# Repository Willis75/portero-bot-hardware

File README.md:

# Portero Bot — Hardware V2

Custom PCB and ESP32 firmware for the Claustro4 gate controller system.

## Overview

Replaces the Raspberry Pi Pico + protoboard + commercial relay board with a professional custom PCB.

- **MCU:** ESP32-WROOM-32E
- **Ethernet:** W5500 (SPI) + HanRun HR911105A RJ45
- **Relays:** 3× dry contact (simulates button press on gate opener controllers)
- **Power:** 9-24V DC barrel jack → 5V buck → 3.3V LDO
- **Programming:** MicroUSB (first flash) + OTA over Ethernet (updates)

## Repository Structure

```
hardware/       KiCad schematic + PCB layout + Gerber files
firmware/       PlatformIO ESP32 firmware (C++)
docs/           BOM, schematic reference, Flux.ai prompt
```

## API

The ESP32 exposes an HTTP API compatible with the existing Node.js bot (no changes required):

```
POST /abrir/vehicular_entrada
POST /abrir/vehicular_salida
POST /abrir/peatonal
GET  /healthz
POST /update   (OTA firmware upload)
```

## Related

- Bot: [Willis75/Portero-bot-telegram](https://github.com/Willis75/Portero-bot-telegram)
- Fabrication: JLCPCB PCBA (~$126 USD / 5 units)

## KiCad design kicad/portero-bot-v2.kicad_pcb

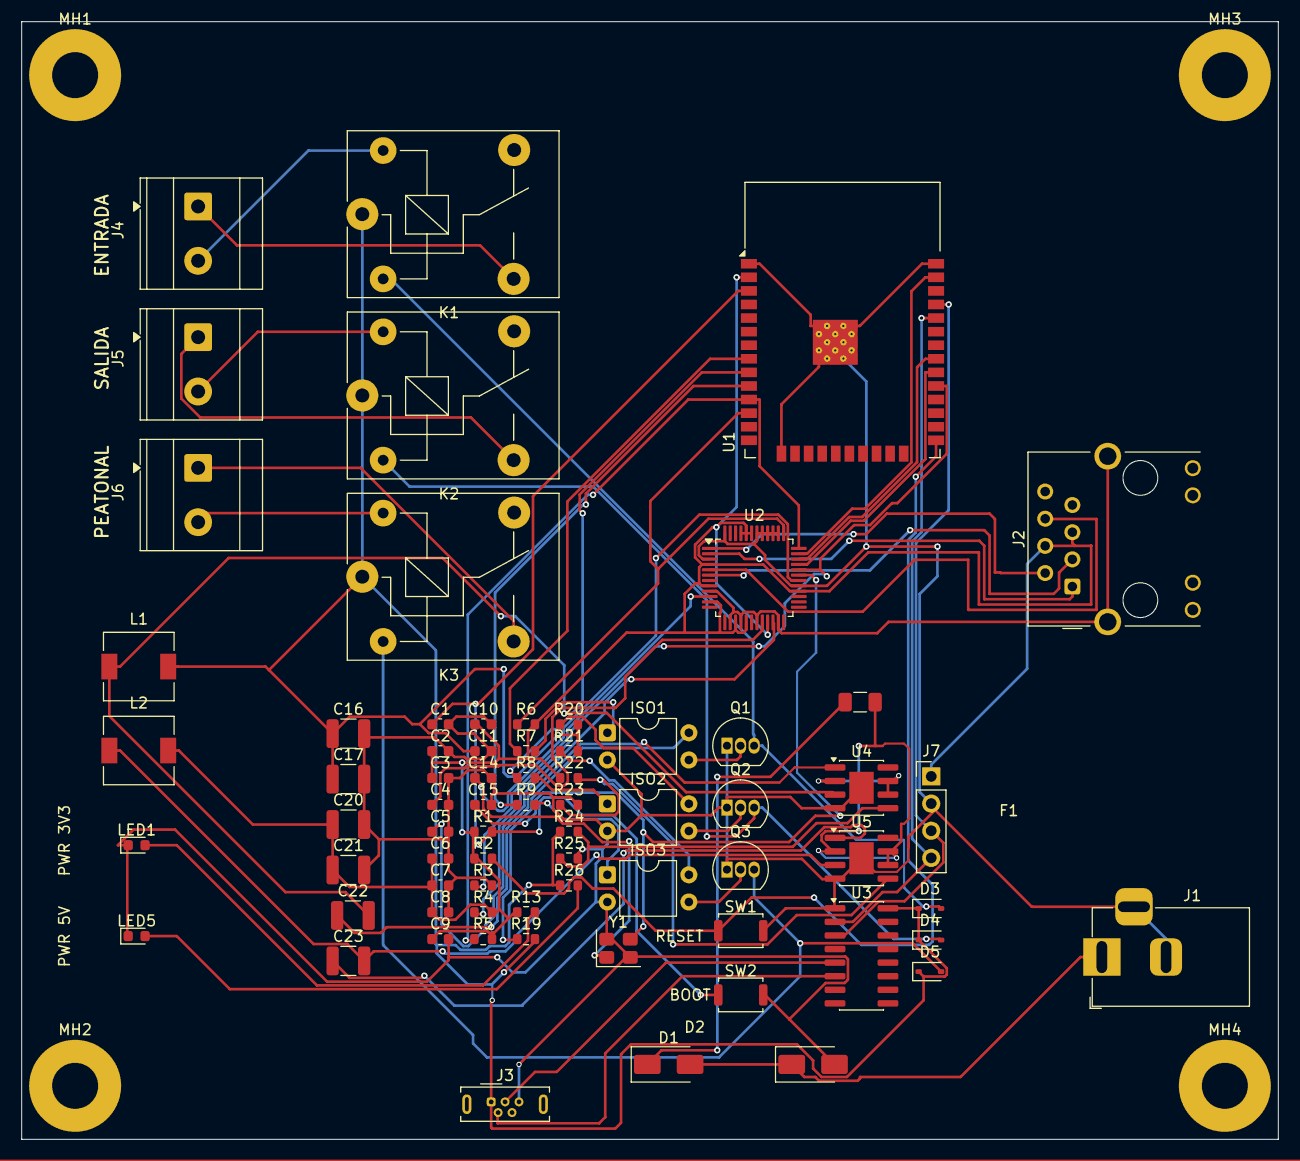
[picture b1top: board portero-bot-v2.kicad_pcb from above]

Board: 2 copper layers, 117.5 x 104.5 mm, 75 parts (0 on the bottom side), 56 nets.

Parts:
C1: 1uF; C_0603_1608Metric
C2, C3, C6, C7, C8, C9, C10, C11: 100nF; C_0603_1608Metric
C4: 4.7uF; C_0603_1608Metric
C5: 10nF; C_0603_1608Metric
C14, C15: 22pF; C_0603_1608Metric
C16, C17, C20, C21: 100uF; C_1210_3225Metric
C22, C23: 100nF; C_1210_3225Metric
D1: SS34-E3/57T; D_SMA
D2: SMAJ24CA-TR; D_SMA
D3, D4, D5: 1N5819WS-7-F; D_SOD-323
F1: 0ZCC0150BF2C; Fuse_1206_3216Metric
ISO1, ISO2, ISO3: PC817X1CSP9F; DIP-4_W7.62mm
J1: DC005; BarrelJack_Horizontal
J2: HR911105A; RJ45_Hanrun_HR911105A_Horizontal
J3: USB Micro B; USB_Micro-B_Wuerth_614105150721_Vertical
J4, J5, J6: KF301-2P; TerminalBlock_Phoenix_MKDS-3-2-5.08_1x02_P5.08mm_Horizontal
J7: Pin Header 01x04 2.54mm Vertical; PinHeader_1x04_P2.54mm_Vertical
K1, K2, K3: SRD-05VDC-SL-C; Relay_SPDT_SANYOU_SRD_Series_Form_C
L1, L2: 22uH; L_6.3x6.3_H3
LED1: KT-0603YG; LED_0603_1608Metric
LED5: KT-0603R; LED_0603_1608Metric
MH1, MH2, MH3, MH4: MountingHole_4.3mm_M4_Pad
Q1, Q2, Q3: 2N2222A; TO-92_Inline
R1, R2, R4, R5, R6, R23, R25: 10k; R_0603_1608Metric
R3: 12.4k; R_0603_1608Metric
R7, R8, R9, R13, R26: 1k; R_0603_1608Metric
R19, R20, R21: 330; R_0603_1608Metric
R22: 26.1k; R_0603_1608Metric
R24: 44.2k; R_0603_1608Metric
SW1, SW2: KH-6X6X5H-STM; SW_Push_SPST_NO_Alps_SKRK
U1: ESP32-WROOM-32E-N16; ESP32-WROOM-32
U2: W5500; LQFP-48_7x7mm_P0.5mm
U3: CH340C; SOIC-16_3.9x9.9mm_P1.27mm
U4, U5: MP2307DN-HW-LF-Z; SOIC-8-1EP_3.9x4.9mm_P1.27mm_EP2.29x3mm
Y1: NX3225GA-25MHZ-STD-CRG-2; Crystal_SMD_3225-4Pin_3.2x2.5mm

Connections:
3V3: C2.1, C3.1, C6.1, C7.1, C8.1, C9.1, C10.1, C20.1, C21.1, J2.4, J2.5, J7.1, L2.2, R1.1, R2.1, R4.2, R5.2, R6.2, R13.1, R22.1, U1.2 (3V3), U2.4 (AVDD), U2.8 (AVDD), U2.11 (AVDD), U2.15 (AVDD), U2.17 (AVDD), U2.21 (AVDD), U2.28 (VDD), U2.43 (PMODE2), U2.44 (PMODE1), U2.45 (PMODE0)
5V: C11.1, C16.1, C17.1, D3.1 (K), D4.1 (K), D5.1 (K), J3.1 (VBUS), K1.1 (A1), K2.1 (A1), K3.1 (A1), L1.2, R19.2, R20.2, R21.2, R24.1, R26.1, U3.16 (VCC)
BOOT: R2.2, SW1.1, U1.25 (IO0)
BST_3V3: C23.1, U5.1 (BS)
BST_5V: C22.1, U4.1 (BS)
EN: C1.1, R1.2, SW2.1, U1.3 (EN)
ETH_CS: R4.1, U1.29 (IO5), U2.32 (~SCS)
ETH_INT: R5.1, U1.11 (IO26), U2.36 (~INT)
ETH_RST: R6.1, U1.12 (IO27), U2.37 (~RST)
ETH_RX_N: J2.6, U2.5 (RXN)
ETH_RX_P: J2.3, U2.6 (RXP)
ETH_TX_N: J2.2, U2.1 (TXN)
ETH_TX_P: J2.1, U2.2 (TXP)
ETH_XI: C14.1, U2.30 (XI/CLKIN), Y1.1
ETH_XO: C15.1, U2.31 (XO), Y1.3
FB_3V3: R22.2, R23.1, U5.5 (FB)
FB_5V: R24.2, R25.1, U4.5 (FB)
GND: C1.2, C2.2, C3.2, C4.2, C5.2, C6.2, C7.2, C8.2, C9.2, C10.2, C11.2, C14.2, C15.2, C16.2, C17.2, C20.2, C21.2, D2.2, ISO1.2 (CATHODE), ISO2.2 (CATHODE), ISO3.2 (CATHODE), J1.2, J1.3, J2.SH, J3.5 (GND), J7.2, LED1.1, LED5.1, Q1.1 (E), Q2.1 (E), Q3.1 (E), R3.2, R23.2, R25.2, SW1.2, SW2.2, U1.1 (GND), U1.15 (GND), U1.38 (GND), U1.39 (GND), U2.3 (AGND), U2.9 (AGND), U2.14 (AGND), U2.16 (AGND), U2.19 (AGND), U2.23 (RSVD), U2.29 (GND), U2.38 (RSVD), U2.39 (RSVD), U2.40 (RSVD), U2.41 (RSVD), U2.42 (RSVD), U2.48 (AGND), U3.1 (GND), U4.4 (GND), U4.9 (EPAD), U5.4 (GND), U5.9 (EPAD), Y1.2 (GND), Y1.4 (GND)
LED5_5V_IND: LED5.2, R26.2
LED_3V3_PWR: LED1.2, R13.2
RELAY1_BASE: ISO1.3 (EMITTER), Q1.2 (B)
RELAY1_COIL_LOW: D3.2 (A), K1.2 (A2), Q1.3 (C)
RELAY1_COM: J4.1, K1.3 (COM)
RELAY1_GPIO: R7.1, U1.8 (IO32)
RELAY1_NO: J4.2, K1.5 (NO)
RELAY1_OPTO_COL: ISO1.4 (COLLECTOR), R19.1
RELAY1_OPTO_LED: ISO1.1 (ANODE), R7.2
RELAY2_BASE: ISO2.3 (EMITTER), Q2.2 (B)
RELAY2_COIL_LOW: D4.2 (A), K2.2 (A2), Q2.3 (C)
RELAY2_COM: J5.1, K2.3 (COM)
RELAY2_GPIO: R8.1, U1.9 (IO33)
RELAY2_NO: J5.2, K2.5 (NO)
RELAY2_OPTO_COL: ISO2.4 (COLLECTOR), R20.1
RELAY2_OPTO_LED: ISO2.1 (ANODE), R8.2
RELAY3_BASE: ISO3.3 (EMITTER), Q3.2 (B)
RELAY3_COIL_LOW: D5.2 (A), K3.2 (A2), Q3.3 (C)
RELAY3_COM: J6.1, K3.3 (COM)
RELAY3_GPIO: R9.1, U1.10 (IO25)
RELAY3_NO: J6.2, K3.5 (NO)
RELAY3_OPTO_COL: ISO3.4 (COLLECTOR), R21.1
RELAY3_OPTO_LED: ISO3.1 (ANODE), R9.2
SPI_MISO: U1.31 (IO19), U2.34 (MISO)
SPI_MOSI: U1.37 (IO23), U2.35 (MOSI)
SPI_SCLK: U1.30 (IO18), U2.33 (SCLK)
SW_BUCK: C22.2, L1.1, U4.3 (SW)
SW_BUCK_3V3: C23.2, L2.1, U5.3 (SW)
UART0_RX: J7.4, U1.34 (RXD0), U3.2 (TXD)
UART0_TX: J7.3, U1.35 (TXD0), U3.3 (RXD)
USB_D_N: J3.2 (D-), U3.6 (UD-)
USB_D_P: J3.3 (D+), U3.5 (UD+)
VIN_BUCK: F1.2, U4.2 (IN), U4.6, U4.7 (EN), U5.2 (IN), U5.6, U5.7 (EN)
VIN_PROT: D1.1 (K), F1.1
VIN_RAW: D1.2 (A), D2.1, J1.1
W5500_1V2O: C5.1, U2.22 (1V2O)
W5500_EXRES: R3.1, U2.10 (EXRES1)
W5500_TOCAP: C4.1, U2.20 (TOCAP)

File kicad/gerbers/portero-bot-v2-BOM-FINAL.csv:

Comment,Designator,Footprint,LCSC Part #,Tier,DNP
0ZCC0150BF2C,F1,Fuse_1206_3216Metric,DNP,Manual,Yes
100nF,"C10,C11,C2,C3,C6,C7,C8,C9",C_0603_1608Metric,C14663,Basic,No
100nF,"C22,C23",C_1210_3225Metric,C141218,Extended,No
100uF,"C16,C17,C20,C21",C_1210_3225Metric,C2840614,Verify,No
10k,"R1,R2,R23,R25,R4,R5,R6",R_0603_1608Metric,C25804,Basic,No
10nF,C5,C_0603_1608Metric,C57112,Basic,No
12.4k,R3,R_0603_1608Metric,C22865,Extended,No
1N5819WS-7-F,"D3,D4,D5",D_SOD-323,C8598,Basic,No
1k,"R13,R26,R7,R8,R9",R_0603_1608Metric,C21190,Basic,No
1uF,C1,C_0603_1608Metric,C15849,Basic,No
22pF,"C14,C15",C_0603_1608Metric,C1653,Basic,No
22uH,"L1,L2",L_6.3x6.3_H3,C354622,Verify,No
26.1k,R22,R_0603_1608Metric,C23356,Extended,No
2N2222A,"Q1,Q2,Q3",TO-92_Inline,DNP,Manual,Yes
330,"R19,R20,R21",R_0603_1608Metric,C23138,Basic,No
4.7uF,C4,C_0603_1608Metric,C19666,Basic,No
44.2k,R24,R_0603_1608Metric,C23056,Extended,No
CH340C,U3,SOIC-16_3.9x9.9mm_P1.27mm,C84681,Extended,No
DC005,J1,BarrelJack_Horizontal,DNP,Manual,Yes
ESP32-WROOM-32E-N16,U1,ESP32-WROOM-32,C701343,Extended,No
HR911105A,J2,RJ45_Hanrun_HR911105A_Horizontal,DNP,Manual,Yes
KF301-2P,"J4,J5,J6",TerminalBlock_Phoenix_MKDS-3-2-5.08_1x02_P5.08mm_Horizontal,DNP,Manual,Yes
KH-6X6X5H-STM,"SW1,SW2",SW_Push_SPST_NO_Alps_SKRK,DNP,Manual,Yes
KT-0603R,LED5,LED_0603_1608Metric,C2286,Basic,No
KT-0603YG,LED1,LED_0603_1608Metric,C2289,Basic,No
MP2307DN-HW-LF-Z,"U4,U5",SOIC-8-1EP_3.9x4.9mm_P1.27mm_EP2.29x3mm,C6306034,Extended,No
NX3225GA-25MHZ-STD-CRG-2,Y1,Crystal_SMD_3225-4Pin_3.2x2.5mm,C438901,Extended,No
PC817X1CSP9F,"ISO1,ISO2,ISO3",DIP-4_W7.62mm,C115500,Verify,No
Pin Header 01x04 2.54mm Vertical,J7,PinHeader_1x04_P2.54mm_Vertical,DNP,Manual,Yes
SMAJ24CA-TR,D2,D_SMA,C148223,Extended,No
SRD-05VDC-SL-C,"K1,K2,K3",Relay_SPDT_SANYOU_SRD_Series_Form_C,DNP,Manual,Yes
SS34-E3/57T,D1,D_SMA,C8678,Basic,No
USB Micro B,J3,USB_Micro-B_Wuerth_614105150721_Vertical,DNP,Manual,Yes
W5500,U2,LQFP-48_7x7mm_P0.5mm,C32843,Extended,No

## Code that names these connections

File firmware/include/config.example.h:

#pragma once
// Copia este archivo a config.h y rellena con credenciales reales.
// config.h esta gitignored.

// === Network ===
// Static IP for Ethernet (preferir static para 24/7, no depende DHCP del router)
#define ETH_USE_STATIC_IP   true
#define ETH_STATIC_IP       "192.168.1.50"
#define ETH_GATEWAY         "192.168.1.1"
#define ETH_SUBNET          "255.255.255.0"
#define ETH_DNS1            "1.1.1.1"
#define ETH_DNS2            "8.8.8.8"

// WiFi backup (si Ethernet falla)
#define WIFI_ENABLED        true
#define WIFI_SSID           "TU_WIFI_SSID"
#define WIFI_PASSWORD       "TU_WIFI_PASSWORD"

// === Auth ===
// Token Bearer para autenticar requests HTTP
// Generate: openssl rand -hex 32
#define API_TOKEN           "REEMPLAZA_CON_TOKEN_HEX_32_BYTES"

// === OTA ===
#define OTA_USERNAME        "admin"
#define OTA_PASSWORD        "REEMPLAZA_CON_PASS_FUERTE"

// === Healthchecks.io (opcional - heartbeat externo) ===
#define HEALTHCHECK_ENABLED true
#define HEALTHCHECK_URL     "https://hc-ping.com/REEMPLAZA-CON-UUID"
#define HEALTHCHECK_PERIOD_MS  60000  // 60 segundos

// === Hardware: pin assignments (NO cambiar - hardware fijo V2) ===
// ESP32-WROOM-32E -> W5500 SPI
#define PIN_ETH_CS          5
#define PIN_ETH_INT         26
#define PIN_ETH_RST         27
#define PIN_SPI_SCK         18
#define PIN_SPI_MISO        19
#define PIN_SPI_MOSI        23

// Reles (GPIO output)
#define PIN_RELAY_ENTRADA   32  // K1 - portón entrada
#define PIN_RELAY_SALIDA    33  // K2 - portón salida
#define PIN_RELAY_PEATONAL  25  // K3 - portón peatonal

// LEDs indicadores (en hardware solo LED1=3V3 y LED5=5V; ningun GPIO controla LED)
// LEDs son indicadores power-on directamente conectados al rail

// === Timing ===
#define RELAY_PULSE_MS      500     // Duracion del cierre de contacto (simula presionar botón)
#define RELAY_COOLDOWN_MS   2000    // Tiempo minimo entre activaciones del mismo relé
#define WATCHDOG_TIMEOUT_S  5       // Task watchdog
#define HTTP_PORT           80

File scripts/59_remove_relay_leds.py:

"""
59 — Remove relay indicator LEDs and their series resistors.

Deletes from PCB:
  - LED2, LED3, LED4 (3x KT-0603R relay-status LEDs)
  - R10, R11, R12 (3x 1k current-limiting resistors)
  - All tracks/vias on nets RELAY1_LED, RELAY2_LED, RELAY3_LED
  - Tracks/vias dangling on RELAY1_GPIO/RELAY2_GPIO/RELAY3_GPIO that were
    routed only to the deleted R10/R11/R12 pads (they will be removed by
    cleaning all tracks on these GPIO nets — they will be re-routed by
    script 58c afterward).

Wait — RELAY2_GPIO and RELAY3_GPIO are ALREADY routed by freerouting
between U1.9-R8.1 and U1.10-R9.1 respectively. Removing R11/R12 should
only delete the *stub* that went to the removed pad. We will leave their
tracks intact; KiCad will mark the R11/R12 connection as unused.

Approach: delete the 6 footprints. Then clean tracks on:
  - RELAY1_LED, RELAY2_LED, RELAY3_LED (entire net)
  - RELAY1_GPIO (entire net — will be re-routed by 58c)
The RELAY2_GPIO and RELAY3_GPIO tracks remain — they connect U1.9↔R8.1
and U1.10↔R9.1 which are still valid net nodes.
"""
import sys
sys.path.insert(0, r"C:\Program Files\KiCad\10.0\bin")
import pcbnew

PCB = r"C:\Users\wumni\Documents\Proyectos\portero-bot-hardware\kicad\portero-bot-v2.kicad_pcb"
board = pcbnew.LoadBoard(PCB)

REMOVE_REFS = {"LED2", "LED3", "LED4", "R10", "R11", "R12"}
PURGE_NETS  = {"RELAY1_LED", "RELAY2_LED", "RELAY3_LED", "RELAY1_GPIO", "BOOT", "BST_5V"}

# Snapshot first to avoid SWIG iterator corruption
fps_to_remove = []
for fp in board.GetFootprints():
    if fp.GetReference() in REMOVE_REFS:
        fps_to_remove.append(fp)

tracks_to_remove = []
for t in list(board.GetTracks()):
    if t.GetNetname() in PURGE_NETS:
        tracks_to_remove.append(t)

print(f"Removing {len(fps_to_remove)} footprints, {len(tracks_to_remove)} tracks/vias")

for fp in fps_to_remove:
    print(f"  - {fp.GetReference()} @({fp.GetPosition().x/1e6:.2f},{fp.GetPosition().y/1e6:.2f})")
    board.Remove(fp)

for t in tracks_to_remove:
    board.Remove(t)

board.Save(PCB)
print(f"\nSaved {PCB}")

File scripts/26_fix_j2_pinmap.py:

"""
26_fix_j2_pinmap.py
Replaces the anonymous "J2.~" pin references in data/nets_clean.json with
explicit pin numbers per the HR911105A datasheet (verified against KiCad
Connector.kicad_sym symbol "RJ45_Hanrun_HR911105A_Horizontal").

Mapping (MAC side of integrated transformer):
  Pin 1 = TD+  -> ETH_TX_P
  Pin 2 = TD-  -> ETH_TX_N
  Pin 3 = RD+  -> ETH_RX_P
  Pin 4 = TCT  -> 3V3 (transmit center tap)
  Pin 5 = RCT  -> 3V3 (receive center tap)
  Pin 6 = RD-  -> ETH_RX_N
  Pins 7,8,9-12 left NC (LEDs ethernet unused).
  SH pads -> GND (already mapped via J2.SHIELD).

Run after 25_remove_relay_leds_from_master.py and before 30_gen_schematic.py.
Idempotent.
"""
import json, os

ROOT = os.path.dirname(os.path.dirname(os.path.abspath(__file__)))
NETS = os.path.join(ROOT, "data", "nets_clean.json")

J2_PIN_BY_NET = {
    "ETH_TX_P": "1",
    "ETH_TX_N": "2",
    "ETH_RX_P": "3",
    "ETH_RX_N": "6",
}

J2_3V3_PINS = ["4", "5"]

nets = json.load(open(NETS, encoding="utf-8"))

updated = []
for n in nets:
    name = n["name"]
    new_pins = []
    changed = False
    for p in n["pins"]:
        if p == "J2.~":
            if name in J2_PIN_BY_NET:
                new_pins.append(f"J2.{J2_PIN_BY_NET[name]}")
                changed = True
                continue
            if name == "3V3":
                continue
            new_pins.append(p)
        else:
            new_pins.append(p)
    if name == "3V3" and any(p.startswith("J2.") for p in n["pins"]):
        if "J2.4" not in new_pins:
            new_pins.append("J2.4")
            changed = True
        if "J2.5" not in new_pins:
            new_pins.append("J2.5")
            changed = True
        new_pins = [p for p in new_pins if p != "J2.~"]
    n["pins"] = new_pins
    if changed:
        updated.append((name, new_pins))

with open(NETS, "w", encoding="utf-8") as f:
    json.dump(nets, f, indent=2, ensure_ascii=False)

print(f"Updated nets: {len(updated)}")
for name, pins in updated:
    j2_pins = [p for p in pins if p.startswith("J2.")]
    print(f"  {name}: J2 pins = {j2_pins}")

remaining = sum(1 for n in nets for p in n["pins"] if p == "J2.~")
print(f"Remaining J2.~ entries: {remaining}")
